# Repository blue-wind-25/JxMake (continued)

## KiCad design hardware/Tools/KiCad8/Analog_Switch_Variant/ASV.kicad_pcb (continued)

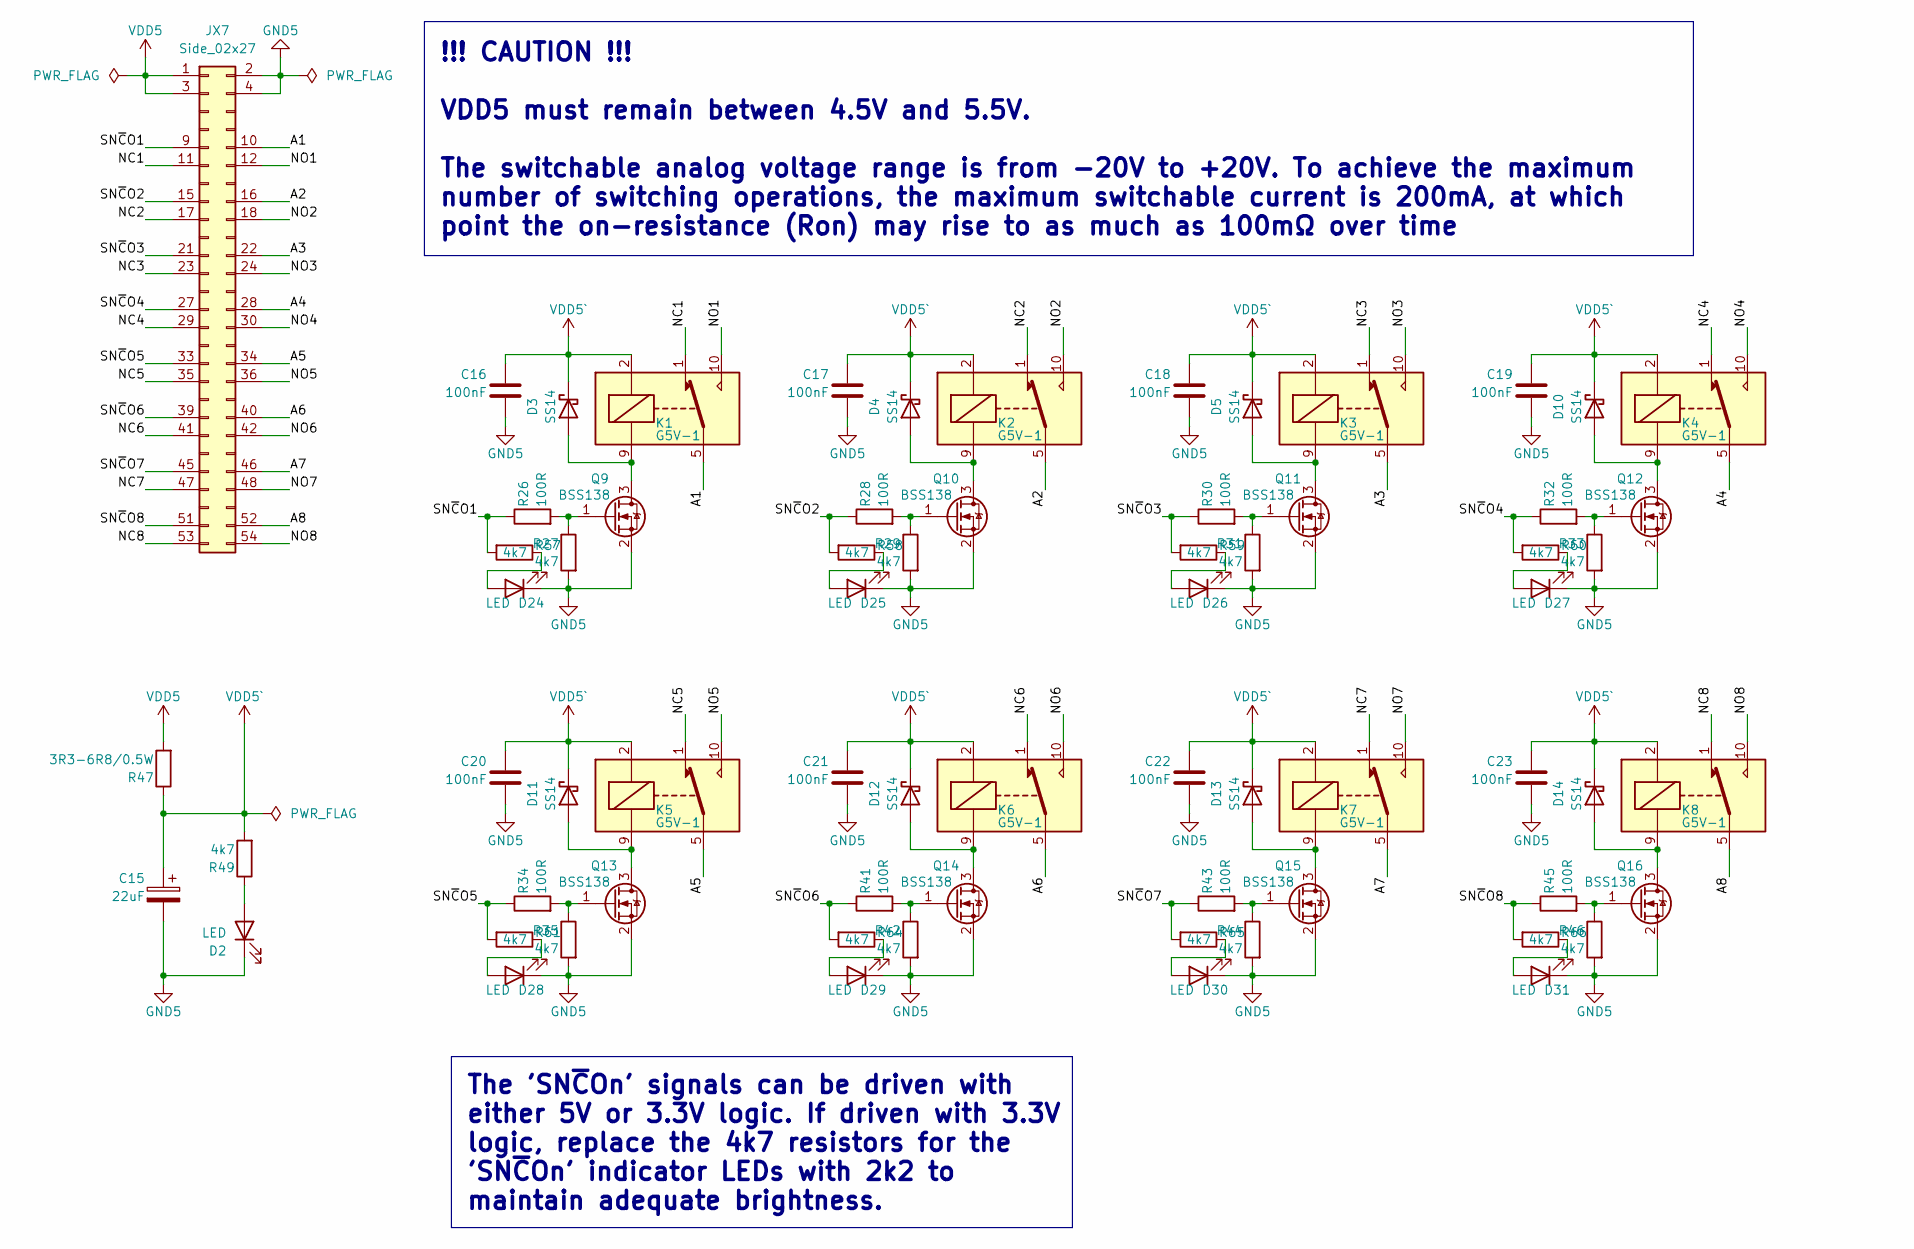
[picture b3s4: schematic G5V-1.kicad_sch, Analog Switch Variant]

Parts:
C15: 22uF; CP_EIA-7360-38_Kemet-E_Pad2.25x4.25mm_HandSolder
C16, C17, C18, C19, C20, C21, C22, C23: 100nF; C_0805_2012Metric_Pad1.18x1.45mm_HandSolder
D2, D24, D25, D26, D27, D28, D29, D30, D31: LED; LED_0805_2012Metric_Pad1.15x1.40mm_HandSolder
D3, D4, D5, D10, D11, D12, D13, D14: SS14; D_SMA
JX7: Side_02x27; PinHeader_2x27_P2.54mm_Vertical
K1, K2, K3, K4, K5, K6, K7, K8: G5V-1; Relay_SPDT_Omron_G5V-1
Q9, Q10, Q11, Q12, Q13, Q14, Q15, Q16: BSS138; SOT-23_Handsoldering
R26, R28, R30, R32, R34, R41, R43, R45: 100R; R_0805_2012Metric_Pad1.20x1.40mm_HandSolder
R27, R29, R31, R33, R35, R42, R44, R46, R49, R57, R58, R59, R60, R61, R64, R65, R66: 4k7; R_0805_2012Metric_Pad1.20x1.40mm_HandSolder
R47: 3R3-6R8/0.5W; R_2010_5025Metric_Pad1.40x2.65mm_HandSolder

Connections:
/G5V-1/A1: JX7.10, K1.5, K1.6
/G5V-1/A2: JX7.16, K2.5, K2.6
/G5V-1/A3: JX7.22, K3.5, K3.6
/G5V-1/A4: JX7.28, K4.5, K4.6
/G5V-1/A5: JX7.34, K5.5, K5.6
/G5V-1/A6: JX7.40, K6.5, K6.6
/G5V-1/A7: JX7.46, K7.5, K7.6
/G5V-1/A8: JX7.52, K8.5, K8.6
/G5V-1/NC1: JX7.11, K1.1
/G5V-1/NC2: JX7.17, K2.1
/G5V-1/NC3: JX7.23, K3.1
/G5V-1/NC4: JX7.29, K4.1
/G5V-1/NC5: JX7.35, K5.1
/G5V-1/NC6: JX7.41, K6.1
/G5V-1/NC7: JX7.47, K7.1
/G5V-1/NC8: JX7.53, K8.1
/G5V-1/NO1: JX7.12, K1.10
/G5V-1/NO2: JX7.18, K2.10
/G5V-1/NO3: JX7.24, K3.10
/G5V-1/NO4: JX7.30, K4.10
/G5V-1/NO5: JX7.36, K5.10
/G5V-1/NO6: JX7.42, K6.10
/G5V-1/NO7: JX7.48, K7.10
/G5V-1/NO8: JX7.54, K8.10
/G5V-1/SN~CO1: JX7.9, R26.1, R57.2
/G5V-1/SN~CO2: JX7.15, R28.1, R58.2
/G5V-1/SN~CO3: JX7.21, R30.1, R59.2
/G5V-1/SN~CO4: JX7.27, R32.1, R60.2
/G5V-1/SN~CO5: JX7.33, R34.1, R61.2
/G5V-1/SN~CO6: JX7.39, R41.1, R64.2
/G5V-1/SN~CO7: JX7.45, R43.1, R65.2
/G5V-1/SN~CO8: JX7.51, R45.1, R66.2
GND5: C15.2, C16.2, C17.2, C18.2, C19.2, C20.2, C21.2, C22.2, C23.2, D2.1 (K), D24.1 (K), D25.1 (K), D26.1 (K), D27.1 (K), D28.1 (K), D29.1 (K), D30.1 (K), D31.1 (K), JX7.2, JX7.4, Q9.2 (S), Q10.2 (S), Q11.2 (S), Q12.2 (S), Q13.2 (S), Q14.2 (S), Q15.2 (S), Q16.2 (S), R27.2, R29.2, R31.2, R33.2, R35.2, R42.2, R44.2, R46.2
unnamed: D2.2 (A), R49.1
unnamed: D3.2 (A), K1.9, Q9.3 (D)
unnamed: D4.2 (A), K2.9, Q10.3 (D)
unnamed: D5.2 (A), K3.9, Q11.3 (D)
unnamed: D10.2 (A), K4.9, Q12.3 (D)
unnamed: D11.2 (A), K5.9, Q13.3 (D)
unnamed: D12.2 (A), K6.9, Q14.3 (D)
unnamed: D13.2 (A), K7.9, Q15.3 (D)
unnamed: D14.2 (A), K8.9, Q16.3 (D)
unnamed: D24.2 (A), R57.1
unnamed: D25.2 (A), R58.1
unnamed: D26.2 (A), R59.1
unnamed: D27.2 (A), R60.1
unnamed: D28.2 (A), R61.1
unnamed: D29.2 (A), R64.1
unnamed: D30.2 (A), R65.1
unnamed: D31.2 (A), R66.1
unnamed: Q9.1 (G), R26.2, R27.1
unnamed: Q10.1 (G), R28.2, R29.1
unnamed: Q11.1 (G), R30.2, R31.1
unnamed: Q12.1 (G), R32.2, R33.1
unnamed: Q13.1 (G), R34.2, R35.1
unnamed: Q14.1 (G), R41.2, R42.1
unnamed: Q15.1 (G), R43.2, R44.1
unnamed: Q16.1 (G), R45.2, R46.1
VDD5: JX7.1, JX7.3, R47.2
VDD5`: C15.1, C16.1, C17.1, C18.1, C19.1, C20.1, C21.1, C22.1, C23.1, D3.1 (K), D4.1 (K), D5.1 (K), D10.1 (K), D11.1 (K), D12.1 (K), D13.1 (K), D14.1 (K), K1.2, K2.2, K3.2, K4.2, K5.2, K6.2, K7.2, K8.2, R47.1, R49.2

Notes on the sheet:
The 'SN~{C}On' signals can be driven with either 5V or 3.3V logic. If driven with 3.3V logic, replace the 4k7 resistors for the 'SN~{C}On' indicator LEDs with 2k2 to maintain adequate brightness.
!!! CAUTION !!! VDD5 must remain between 4.5V and 5.5V. The switchable analog voltage range is from -20V to +20V. To achieve the maximum number of switching operations, the maximum switchable current is 200mA, at which point the on-resistance (Ron) may rise to as much as 100mΩ over time

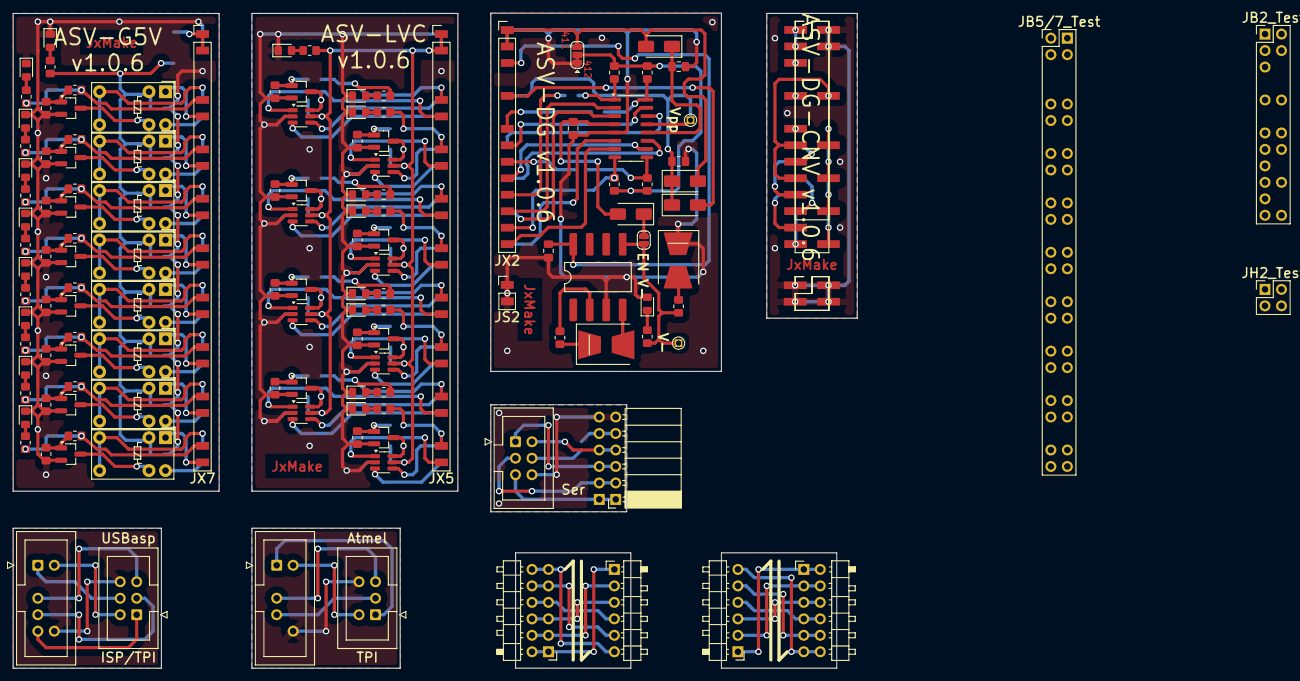
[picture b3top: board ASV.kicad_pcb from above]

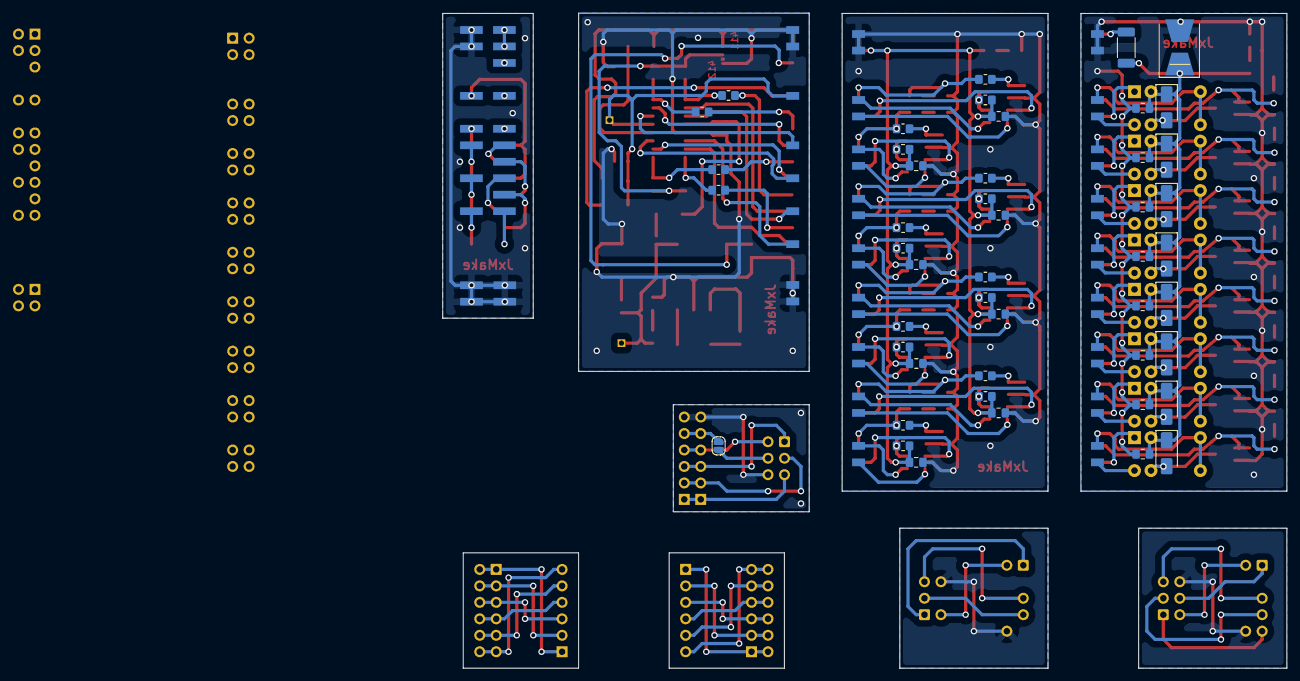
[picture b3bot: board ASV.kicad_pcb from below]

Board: 2 copper layers, 130.2 x 101.0 mm, 184 parts (47 on the bottom side), 195 nets.

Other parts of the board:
JB2_Test: Conn_02x12; PinHeader_2x12_P2.54mm_Vertical
JB5/7_Test: Conn_02x27; PinHeader_2x27_P2.54mm_Vertical
JBx2: Side_02x14; PinHeader_2x14_P2.54mm_Vertical
JH2_Test: Stabilizer; PinHeader_2x02_P2.54mm_Vertical

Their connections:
/DG41xDY_with_Converter/Ctl1`: JBx2.21; also elsewhere on the board
/DG41xDY_with_Converter/Ctl2`: JBx2.13; also elsewhere on the board
/DG41xDY_with_Converter/Ctl3`: JBx2.17; also elsewhere on the board
/DG41xDY_with_Converter/Ctl4`: JBx2.25; also elsewhere on the board
/DG41xDY_with_Converter/D1`: JBx2.23; also elsewhere on the board
/DG41xDY_with_Converter/D4`: JBx2.27; also elsewhere on the board
/DG41xDY_with_Converter/S1`: JBx2.24; also elsewhere on the board
/DG41xDY_with_Converter/S4`: JBx2.28; also elsewhere on the board
/DG41xDY_with_Converter/VBoost_In`: JBx2.9; also elsewhere on the board
/DG41xDY_with_Converter/Vpp2`: JBx2.16; also elsewhere on the board
/DG41xDY_with_Converter/Vpp3`: JBx2.20; also elsewhere on the board
/DG41xDY_with_Converter/Vpp_Out`: JBx2.10, JBx2.15, JBx2.19; also elsewhere on the board
GND`2: JBx2.2, JBx2.4; also elsewhere on the board
VDD`2: JBx2.1, JBx2.3; also elsewhere on the board
VDD`2_47: JBx2.5; also elsewhere on the board

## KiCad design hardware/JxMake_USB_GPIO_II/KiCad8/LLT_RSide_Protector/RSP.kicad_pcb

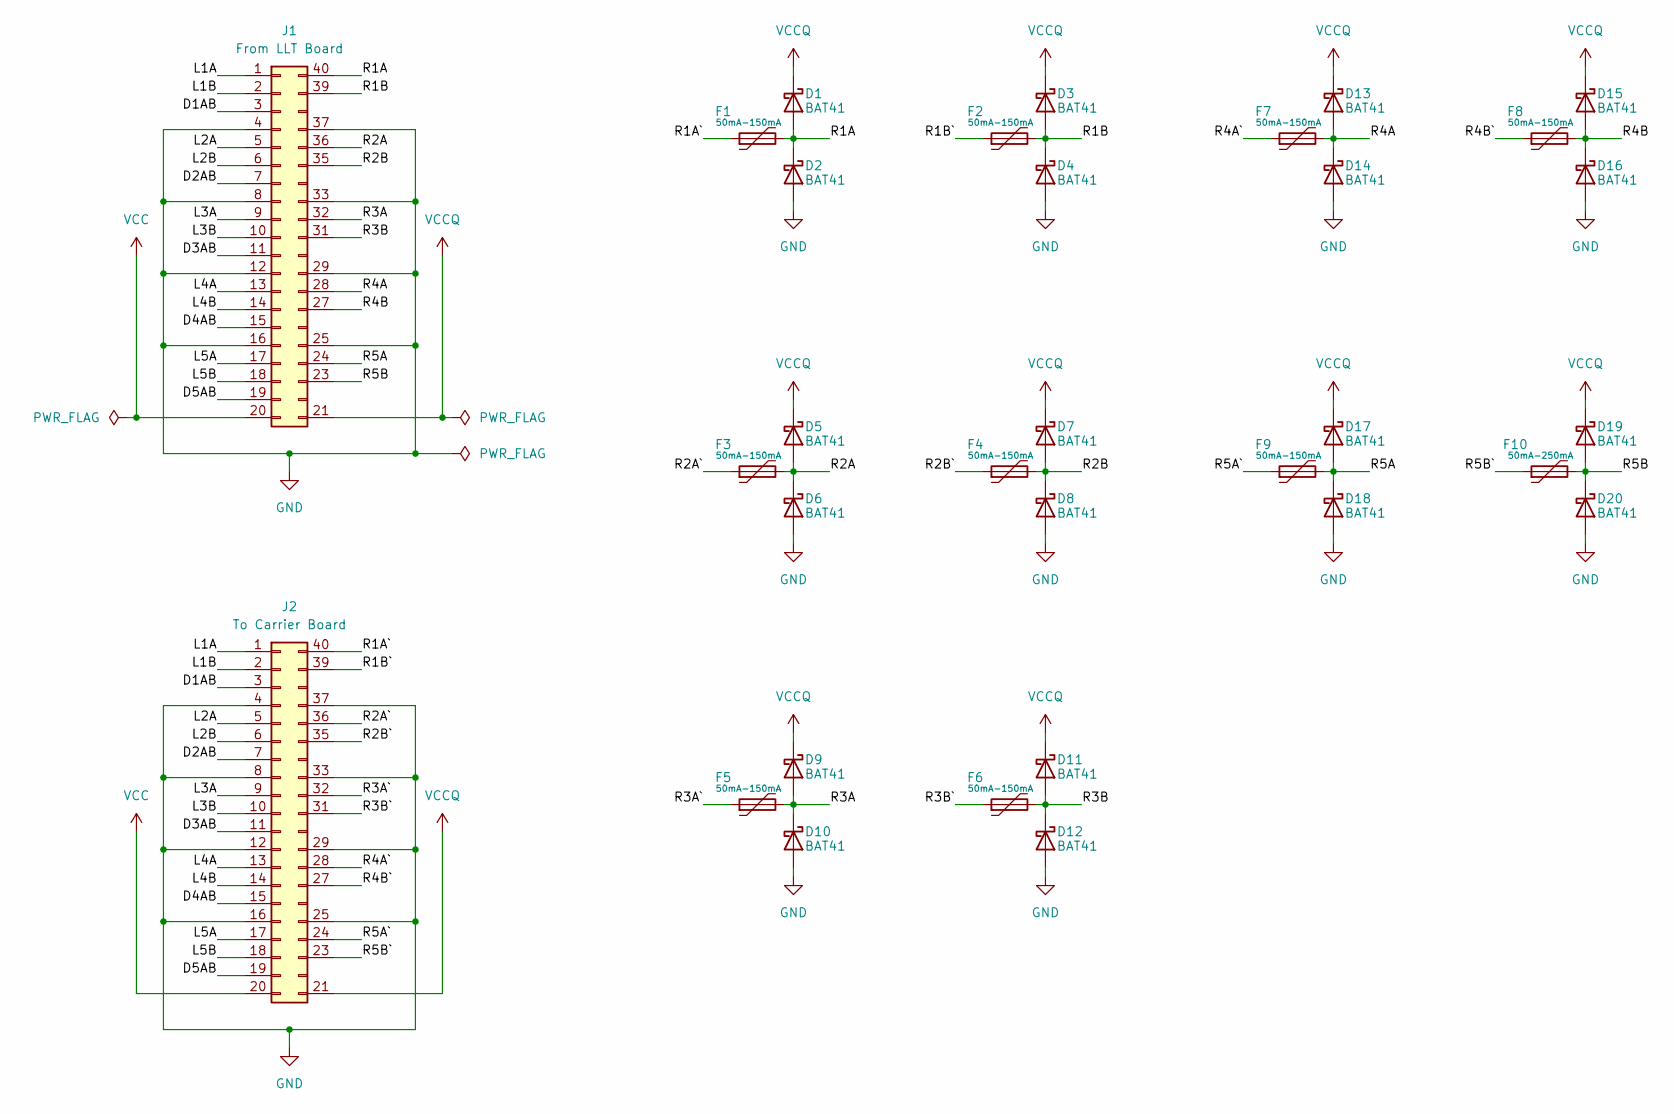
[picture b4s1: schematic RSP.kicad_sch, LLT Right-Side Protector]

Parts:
D1, D2, D3, D4, D5, D6, D7, D8, D9, D10, D11, D12, D13, D14, D15, D16, D17, D18, D19, D20: BAT41; D_DO-35_SOD27_P7.62mm_Horizontal
F1, F2, F3, F4, F5, F6, F7, F8, F9: 50mA-150mA; R_1210_3225Metric_Pad1.30x2.65mm_HandSolder
F10: 50mA-250mA; R_1210_3225Metric_Pad1.30x2.65mm_HandSolder
J1: From LLT Board; DIP-40_W25.4mm_LongPads
J2: To Carrier Board; DIP-40_W25.4mm_LongPads

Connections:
/D1AB: J1.3, J2.3
/D2AB: J1.7, J2.7
/D3AB: J1.11, J2.11
/D4AB: J1.15, J2.15
/D5AB: J1.19, J2.19
/L1A: J1.1, J2.1
/L1B: J1.2, J2.2
/L2A: J1.5, J2.5
/L2B: J1.6, J2.6
/L3A: J1.9, J2.9
/L3B: J1.10, J2.10
/L4A: J1.13, J2.13
/L4B: J1.14, J2.14
/L5A: J1.17, J2.17
/L5B: J1.18, J2.18
/R1A: D1.2 (A), D2.1 (K), F1.2, J1.40
/R1A`: F1.1, J2.40
/R1B: D3.2 (A), D4.1 (K), F2.2, J1.39
/R1B`: F2.1, J2.39
/R2A: D5.2 (A), D6.1 (K), F3.2, J1.36
/R2A`: F3.1, J2.36
/R2B: D7.2 (A), D8.1 (K), F4.2, J1.35
/R2B`: F4.1, J2.35
/R3A: D9.2 (A), D10.1 (K), F5.2, J1.32
/R3A`: F5.1, J2.32
/R3B: D11.2 (A), D12.1 (K), F6.2, J1.31
/R3B`: F6.1, J2.31
/R4A: D13.2 (A), D14.1 (K), F7.2, J1.28
/R4A`: F7.1, J2.28
/R4B: D15.2 (A), D16.1 (K), F8.2, J1.27
/R4B`: F8.1, J2.27
/R5A: D17.2 (A), D18.1 (K), F9.2, J1.24
/R5A`: F9.1, J2.24
/R5B: D19.2 (A), D20.1 (K), F10.2, J1.23
/R5B`: F10.1, J2.23
GND: D2.2 (A), D4.2 (A), D6.2 (A), D8.2 (A), D10.2 (A), D12.2 (A), D14.2 (A), D16.2 (A), D18.2 (A), D20.2 (A), J1.4, J1.8, J1.12, J1.16, J1.25, J1.29, J1.33, J1.37, J2.4, J2.8, J2.12, J2.16, J2.25, J2.29, J2.33, J2.37
VCC: J1.20, J2.20
VCCQ: D1.1 (K), D3.1 (K), D5.1 (K), D7.1 (K), D9.1 (K), D11.1 (K), D13.1 (K), D15.1 (K), D17.1 (K), D19.1 (K), J1.21, J2.21

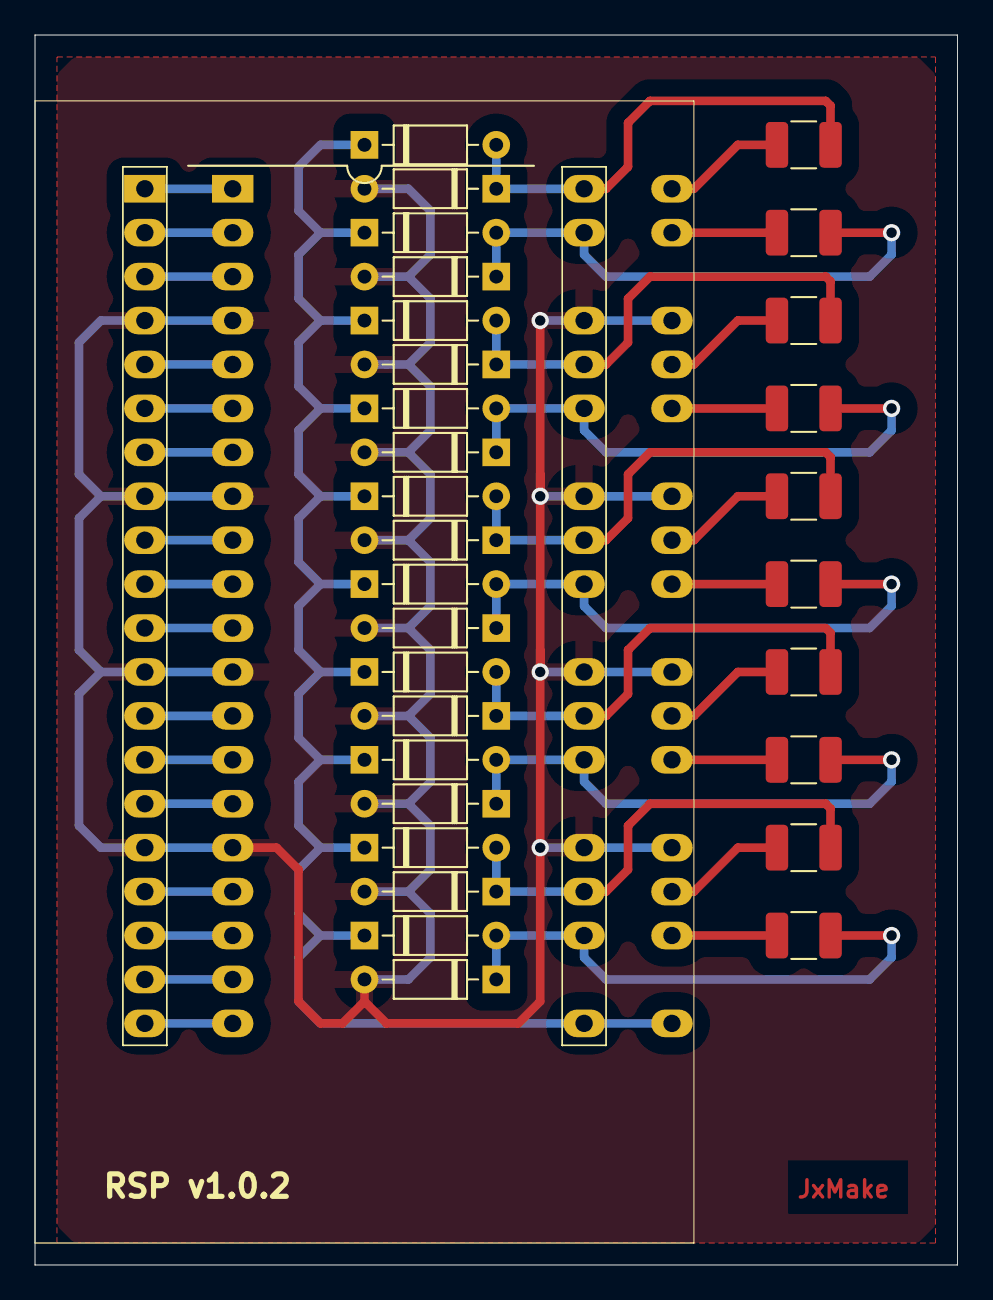
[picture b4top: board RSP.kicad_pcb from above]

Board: 2 copper layers, 53.3 x 71.1 mm, 32 parts (0 on the bottom side), 38 nets.

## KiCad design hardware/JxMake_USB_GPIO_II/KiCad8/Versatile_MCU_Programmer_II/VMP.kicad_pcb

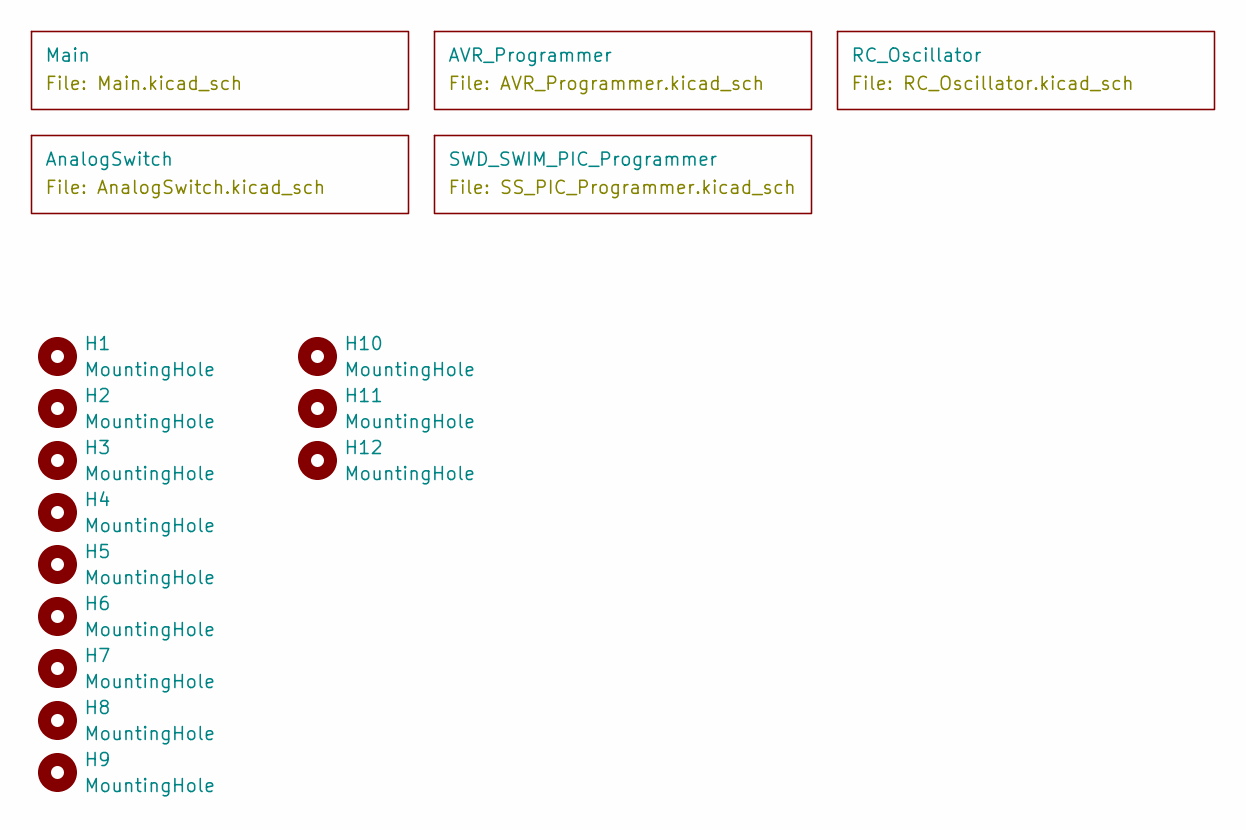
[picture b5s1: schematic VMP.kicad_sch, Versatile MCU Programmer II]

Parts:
H1, H2, H3, H4, H5, H6, H7, H8, H9: MountingHole; MountingHole_3.2mm_M3
H10, H11, H12: MountingHole; MountingHole_2.2mm_M2

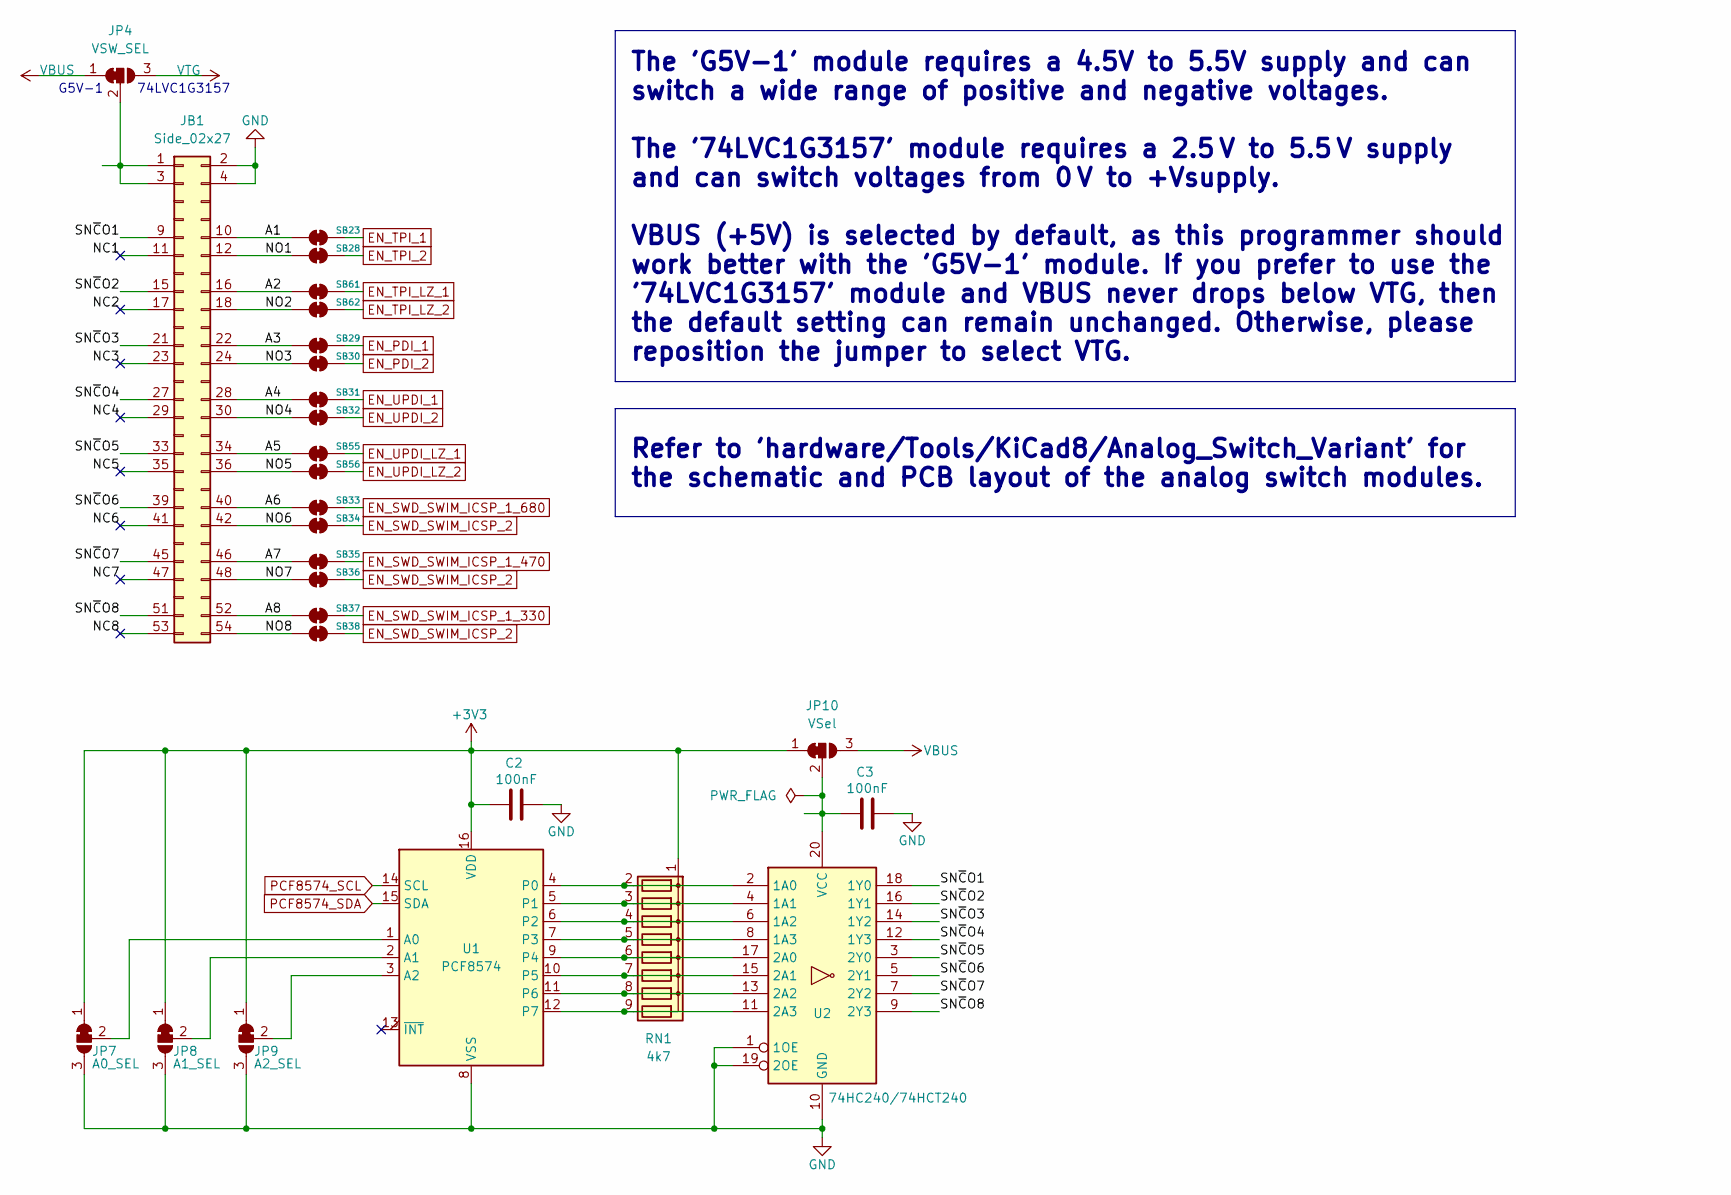
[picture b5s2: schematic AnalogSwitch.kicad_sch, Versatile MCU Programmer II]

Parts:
C2, C3: 100nF; C_0805_2012Metric_Pad1.18x1.45mm_HandSolder
JB1: Side_02x27; PinHeader_2x27_P2.54mm_Vertical
JP4: VSW_SEL; SolderJumper-3_P1.3mm_Bridged12_RoundedPad1.0x1.5mm
JP7: A0_SEL; SolderJumper-3_P1.3mm_Bridged12_RoundedPad1.0x1.5mm
JP8: A1_SEL; SolderJumper-3_P1.3mm_Bridged12_RoundedPad1.0x1.5mm
JP9: A2_SEL; SolderJumper-3_P1.3mm_Bridged12_RoundedPad1.0x1.5mm
JP10: VSel; SolderJumper-3_P1.3mm_Bridged12_RoundedPad1.0x1.5mm
RN1: 4k7; R_Array_SIP9
SB23, SB28, SB29, SB30, SB31, SB32, SB33, SB34, SB35, SB36, SB37, SB38, SB55, SB56, SB61, SB62: Jumper_2_Small_Bridged; SolderJumper-2_P1.3mm_Bridged_Pad1.0x1.5mm
U1: PCF8574; SOIC-16W_7.5x10.3mm_P1.27mm
U2: 74HC240/74HCT240; SOIC-20W_7.5x12.8mm_P1.27mm

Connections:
+3V3: C2.1, JP7.1 (A), JP8.1 (A), JP9.1 (A), JP10.1 (A), RN1.1 (common), U1.16 (VDD); also elsewhere on the board
/AnalogSwitch/A1: JB1.10, SB23.2 (B)
/AnalogSwitch/A2: JB1.16, SB61.2 (B)
/AnalogSwitch/A3: JB1.22, SB29.2 (B)
/AnalogSwitch/A4: JB1.28, SB31.2 (B)
/AnalogSwitch/A5: JB1.34, SB55.2 (B)
/AnalogSwitch/A6: JB1.40, SB33.2 (B)
/AnalogSwitch/A7: JB1.46, SB35.2 (B)
/AnalogSwitch/A8: JB1.52, SB37.2 (B)
/AnalogSwitch/NC1: JB1.11
/AnalogSwitch/NC2: JB1.17
/AnalogSwitch/NC3: JB1.23
/AnalogSwitch/NC4: JB1.29
/AnalogSwitch/NC5: JB1.35
/AnalogSwitch/NC6: JB1.41
/AnalogSwitch/NC7: JB1.47
/AnalogSwitch/NC8: JB1.53
/AnalogSwitch/NO1: JB1.12, SB28.2 (B)
/AnalogSwitch/NO2: JB1.18, SB62.2 (B)
/AnalogSwitch/NO3: JB1.24, SB30.2 (B)
/AnalogSwitch/NO4: JB1.30, SB32.2 (B)
/AnalogSwitch/NO5: JB1.36, SB56.2 (B)
/AnalogSwitch/NO6: JB1.42, SB34.2 (B)
/AnalogSwitch/NO7: JB1.48, SB36.2 (B)
/AnalogSwitch/NO8: JB1.54, SB38.2 (B)
/AnalogSwitch/SN~CO1: JB1.9, U2.18 (1Y0)
/AnalogSwitch/SN~CO2: JB1.15, U2.16 (1Y1)
/AnalogSwitch/SN~CO3: JB1.21, U2.14 (1Y2)
/AnalogSwitch/SN~CO4: JB1.27, U2.12 (1Y3)
/AnalogSwitch/SN~CO5: JB1.33, U2.3 (2Y0)
/AnalogSwitch/SN~CO6: JB1.39, U2.5 (2Y1)
/AnalogSwitch/SN~CO7: JB1.45, U2.7 (2Y2)
/AnalogSwitch/SN~CO8: JB1.51, U2.9 (2Y3)
EN_PDI_1: SB29.1 (A); also elsewhere on the board
EN_PDI_2: SB30.1 (A); also elsewhere on the board
EN_SWD_SWIM_ICSP_1_330: SB37.1 (A); also elsewhere on the board
EN_SWD_SWIM_ICSP_1_470: SB35.1 (A); also elsewhere on the board
EN_SWD_SWIM_ICSP_1_680: SB33.1 (A); also elsewhere on the board
EN_SWD_SWIM_ICSP_2: SB34.1 (A), SB36.1 (A), SB38.1 (A); also elsewhere on the board
EN_TPI_1: SB23.1 (A); also elsewhere on the board
EN_TPI_2: SB28.1 (A); also elsewhere on the board
EN_TPI_LZ_1: SB61.1 (A); also elsewhere on the board
EN_TPI_LZ_2: SB62.1 (A); also elsewhere on the board
EN_UPDI_1: SB31.1 (A); also elsewhere on the board
EN_UPDI_2: SB32.1 (A); also elsewhere on the board
EN_UPDI_LZ_1: SB55.1 (A); also elsewhere on the board
EN_UPDI_LZ_2: SB56.1 (A); also elsewhere on the board
GND: C2.2, C3.2, JB1.2, JB1.4, JP7.3 (B), JP8.3 (B), JP9.3 (B), U1.8 (VSS), U2.1 (1OE), U2.10 (GND), U2.19 (2OE); also elsewhere on the board
unnamed: JB1.1, JB1.3, JP4.2 (C)
unnamed: JP7.2 (C), U1.1 (A0)
unnamed: JP8.2 (C), U1.2 (A1)
unnamed: JP9.2 (C), U1.3 (A2)
unnamed: C3.1, JP10.2 (C), U2.20 (VCC)
unnamed: RN1.2 (R1), U1.4 (P0), U2.2 (1A0)
unnamed: RN1.3 (R2), U1.5 (P1), U2.4 (1A1)
unnamed: RN1.4 (R3), U1.6 (P2), U2.6 (1A2)
unnamed: RN1.5 (R4), U1.7 (P3), U2.8 (1A3)
unnamed: RN1.6 (R5), U1.9 (P4), U2.17 (2A0)
unnamed: RN1.7 (R6), U1.10 (P5), U2.15 (2A1)
unnamed: RN1.8 (R7), U1.11 (P6), U2.13 (2A2)
unnamed: RN1.9 (R8), U1.12 (P7), U2.11 (2A3)
PCF8574_SCL: U1.14 (SCL); also elsewhere on the board
PCF8574_SDA: U1.15 (SDA); also elsewhere on the board
VBUS: JP4.1 (A), JP10.3 (B); also elsewhere on the board
VTG: JP4.3 (B); also elsewhere on the board

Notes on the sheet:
Refer to 'hardware/Tools/KiCad8/Analog_Switch_Variant' for the schematic and PCB layout of the analog switch modules.
The 'G5V-1' module requires a 4.5V to 5.5V supply and can switch a wide range of positive and negative voltages. The '74LVC1G3157' module requires a 2.5 V to 5.5 V supply and can switch voltages from 0 V to +Vsupply. VBUS (+5V) is selected by default, as this programmer should work better with the 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
G5V-1
74LVC1G3157

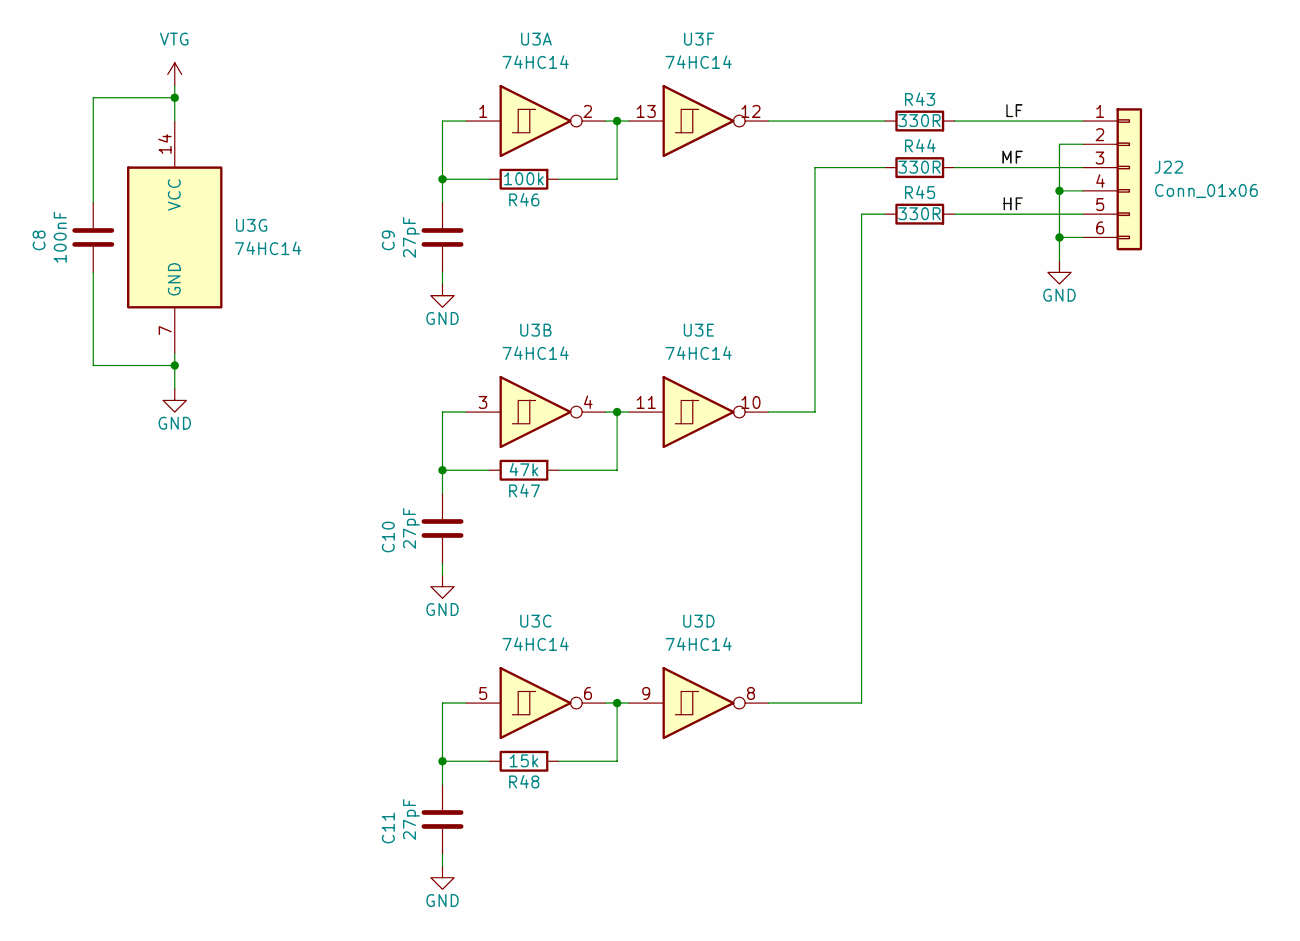
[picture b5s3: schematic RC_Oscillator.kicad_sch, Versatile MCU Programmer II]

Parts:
C8: 100nF; C_0805_2012Metric_Pad1.18x1.45mm_HandSolder
C9, C10, C11: 27pF; C_0805_2012Metric_Pad1.18x1.45mm_HandSolder
J22: Conn_01x06; PinHeader_1x06_P2.54mm_Horizontal
R43, R44, R45: 330R; R_0805_2012Metric_Pad1.20x1.40mm_HandSolder
R46: 100k; R_0805_2012Metric_Pad1.20x1.40mm_HandSolder
R47: 47k; R_0805_2012Metric_Pad1.20x1.40mm_HandSolder
R48: 15k; R_0805_2012Metric_Pad1.20x1.40mm_HandSolder
U3: 74HC14

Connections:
/RC_Oscillator/HF: J22.5, R45.2
/RC_Oscillator/LF: J22.1, R43.2
/RC_Oscillator/MF: J22.3, R44.2
GND: C8.1, C9.1, C10.1, C11.1, J22.2, J22.4, J22.6, U3.7 (GND); also elsewhere on the board
unnamed: C9.2, R46.1, U3.1
unnamed: C10.2, R47.1, U3.3
unnamed: C11.2, R48.1, U3.5
unnamed: R43.1, U3.12
unnamed: R44.1, U3.10
unnamed: R45.1, U3.8
unnamed: R46.2, U3.2, U3.13
unnamed: R47.2, U3.4, U3.11
unnamed: R48.2, U3.6, U3.9
VTG: C8.2, U3.14 (VCC); also elsewhere on the board

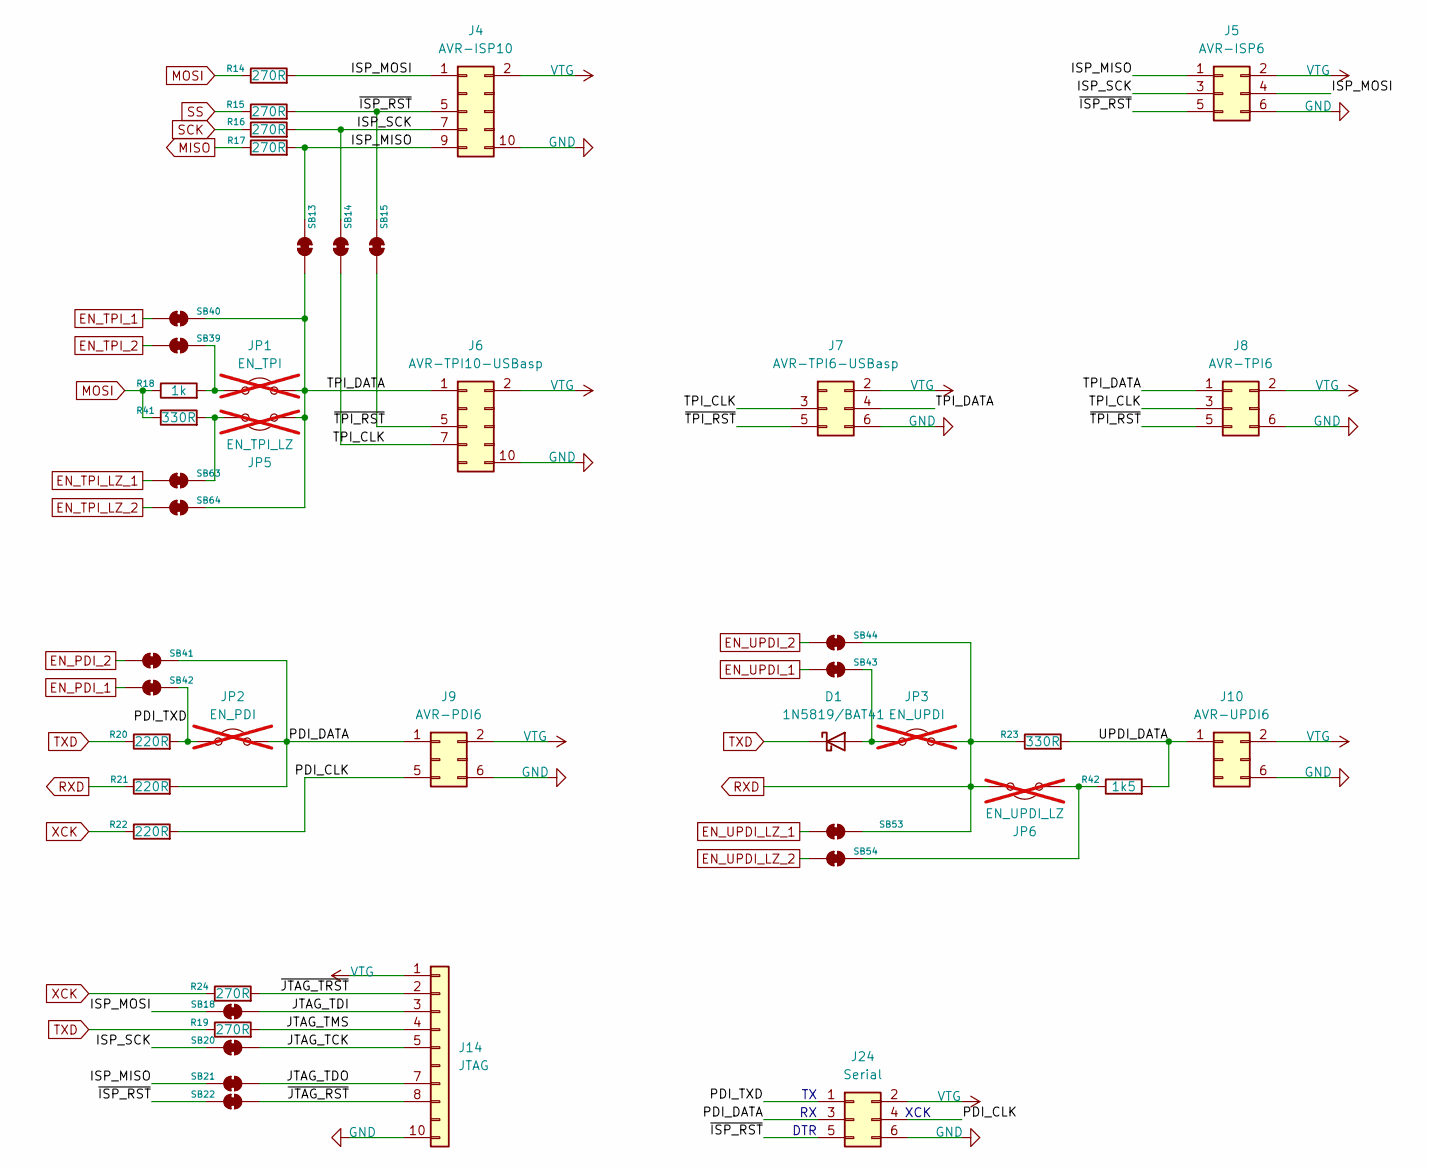
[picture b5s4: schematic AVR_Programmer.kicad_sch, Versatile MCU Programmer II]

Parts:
D1: 1N5819/BAT41; D_SMA_Handsoldering
J4: AVR-ISP10; IDC-Header_2x05_P2.54mm_Vertical
J5: AVR-ISP6; IDC-Header_2x03_P2.54mm_Vertical
J6: AVR-TPI10-USBasp; IDC-Header_2x05_P2.54mm_Vertical
J7: AVR-TPI6-USBasp; IDC-Header_2x03_P2.54mm_Vertical
J8: AVR-TPI6; IDC-Header_2x03_P2.54mm_Vertical
J9: AVR-PDI6; IDC-Header_2x03_P2.54mm_Vertical
J10: AVR-UPDI6; IDC-Header_2x03_P2.54mm_Vertical
J14: JTAG; PinSocket_1x10_P2.54mm_Horizontal
J24: Serial; IDC-Header_2x03_P2.54mm_Vertical
JP1: EN_TPI; PinHeader_1x02_P2.54mm_Vertical; not fitted
JP2: EN_PDI; PinHeader_1x02_P2.54mm_Vertical; not fitted
JP3: EN_UPDI; PinHeader_1x02_P2.54mm_Vertical; not fitted
JP5: EN_TPI_LZ; PinHeader_1x02_P2.54mm_Vertical; not fitted
JP6: EN_UPDI_LZ; PinHeader_1x02_P2.54mm_Vertical; not fitted
R14, R15, R16, R17: 270R; R_1206_3216Metric_Pad1.30x1.75mm_HandSolder
R18: 1k; R_0805_2012Metric_Pad1.20x1.40mm_HandSolder
R19, R24: 270R; R_0805_2012Metric_Pad1.20x1.40mm_HandSolder
R20, R21, R22: 220R; R_0805_2012Metric_Pad1.20x1.40mm_HandSolder
R23, R41: 330R; R_1206_3216Metric_Pad1.30x1.75mm_HandSolder
R42: 1k5; R_0805_2012Metric_Pad1.20x1.40mm_HandSolder
SB13, SB14, SB15, SB18, SB20, SB21, SB22, SB39, SB40, SB41, SB42, SB43, SB44, SB53, SB54, SB63, SB64: Jumper_2_Small_Bridged; SolderJumper-2_P1.3mm_Bridged_Pad1.0x1.5mm

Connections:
/AVR_Programmer/ISP_MISO: J4.9, J5.1, R17.2, SB13.1 (A), SB21.1 (A)
/AVR_Programmer/ISP_MOSI: J4.1, J5.4, R14.2, SB18.1 (A)
/AVR_Programmer/ISP_SCK: J4.7, J5.3, R16.2, SB14.1 (A), SB20.1 (A)
/AVR_Programmer/JTAG_TCK: J14.5, SB20.2 (B)
/AVR_Programmer/JTAG_TDI: J14.3, SB18.2 (B)
/AVR_Programmer/JTAG_TDO: J14.7, SB21.2 (B)
/AVR_Programmer/JTAG_TMS: J14.4, R19.2
/AVR_Programmer/PDI_CLK: J9.5, J24.4, R22.2
/AVR_Programmer/PDI_DATA: J9.1, J24.3, JP2.2 (B), R21.2, SB41.1 (A)
/AVR_Programmer/PDI_TXD: J24.1, JP2.1 (A), R20.2, SB42.1 (A)
/AVR_Programmer/TPI_CLK: J6.7, J7.3, J8.3, SB14.2 (B)
/AVR_Programmer/TPI_DATA: J6.1, J7.4, J8.1, JP1.2 (B), JP5.2 (B), SB13.2 (B), SB40.1 (A), SB64.1 (A)
/AVR_Programmer/UPDI_DATA: J10.1, R23.2, R42.2
/AVR_Programmer/~ISP_RST: J4.5, J5.5, J24.5, R15.2, SB15.1 (A), SB22.1 (A)
/AVR_Programmer/~JTAG_RST: J14.8, SB22.2 (B)
/AVR_Programmer/~JTAG_TRST: J14.2, R24.2
/AVR_Programmer/~TPI_RST: J6.5, J7.5, J8.5, SB15.2 (B)
EN_PDI_1: SB42.2 (B); also elsewhere on the board
EN_PDI_2: SB41.2 (B); also elsewhere on the board
EN_TPI_1: SB40.2 (B); also elsewhere on the board
EN_TPI_2: SB39.2 (B); also elsewhere on the board
EN_TPI_LZ_1: SB63.2 (B); also elsewhere on the board
EN_TPI_LZ_2: SB64.2 (B); also elsewhere on the board
EN_UPDI_1: SB43.2 (B); also elsewhere on the board
EN_UPDI_2: SB44.2 (B); also elsewhere on the board
EN_UPDI_LZ_1: SB53.2 (B); also elsewhere on the board
EN_UPDI_LZ_2: SB54.2 (B); also elsewhere on the board
GND: J4.10, J5.6, J6.10, J7.6, J8.6, J9.6, J10.6, J14.10, J24.6; also elsewhere on the board
MISO: R17.1; also elsewhere on the board
MOSI: R14.1, R18.1, R41.1; also elsewhere on the board
unnamed: D1.2 (A), JP3.1 (A), SB43.1 (A)
unnamed: JP1.1 (A), R18.2, SB39.1 (A)
unnamed: JP5.1 (A), R41.2, SB63.1 (A)
unnamed: JP6.2 (B), R42.1, SB54.1 (A)
RXD: JP3.2 (B), JP6.1 (A), R21.1, R23.1, SB44.1 (A), SB53.1 (A); also elsewhere on the board
SCK: R16.1; also elsewhere on the board
SS: R15.1; also elsewhere on the board
TXD: D1.1 (K), R19.1, R20.1; also elsewhere on the board
VTG: J4.2, J5.2, J6.2, J7.2, J8.2, J9.2, J10.2, J14.1, J24.2; also elsewhere on the board
XCK: R22.1, R24.1; also elsewhere on the board

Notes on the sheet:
DTR
XCK
